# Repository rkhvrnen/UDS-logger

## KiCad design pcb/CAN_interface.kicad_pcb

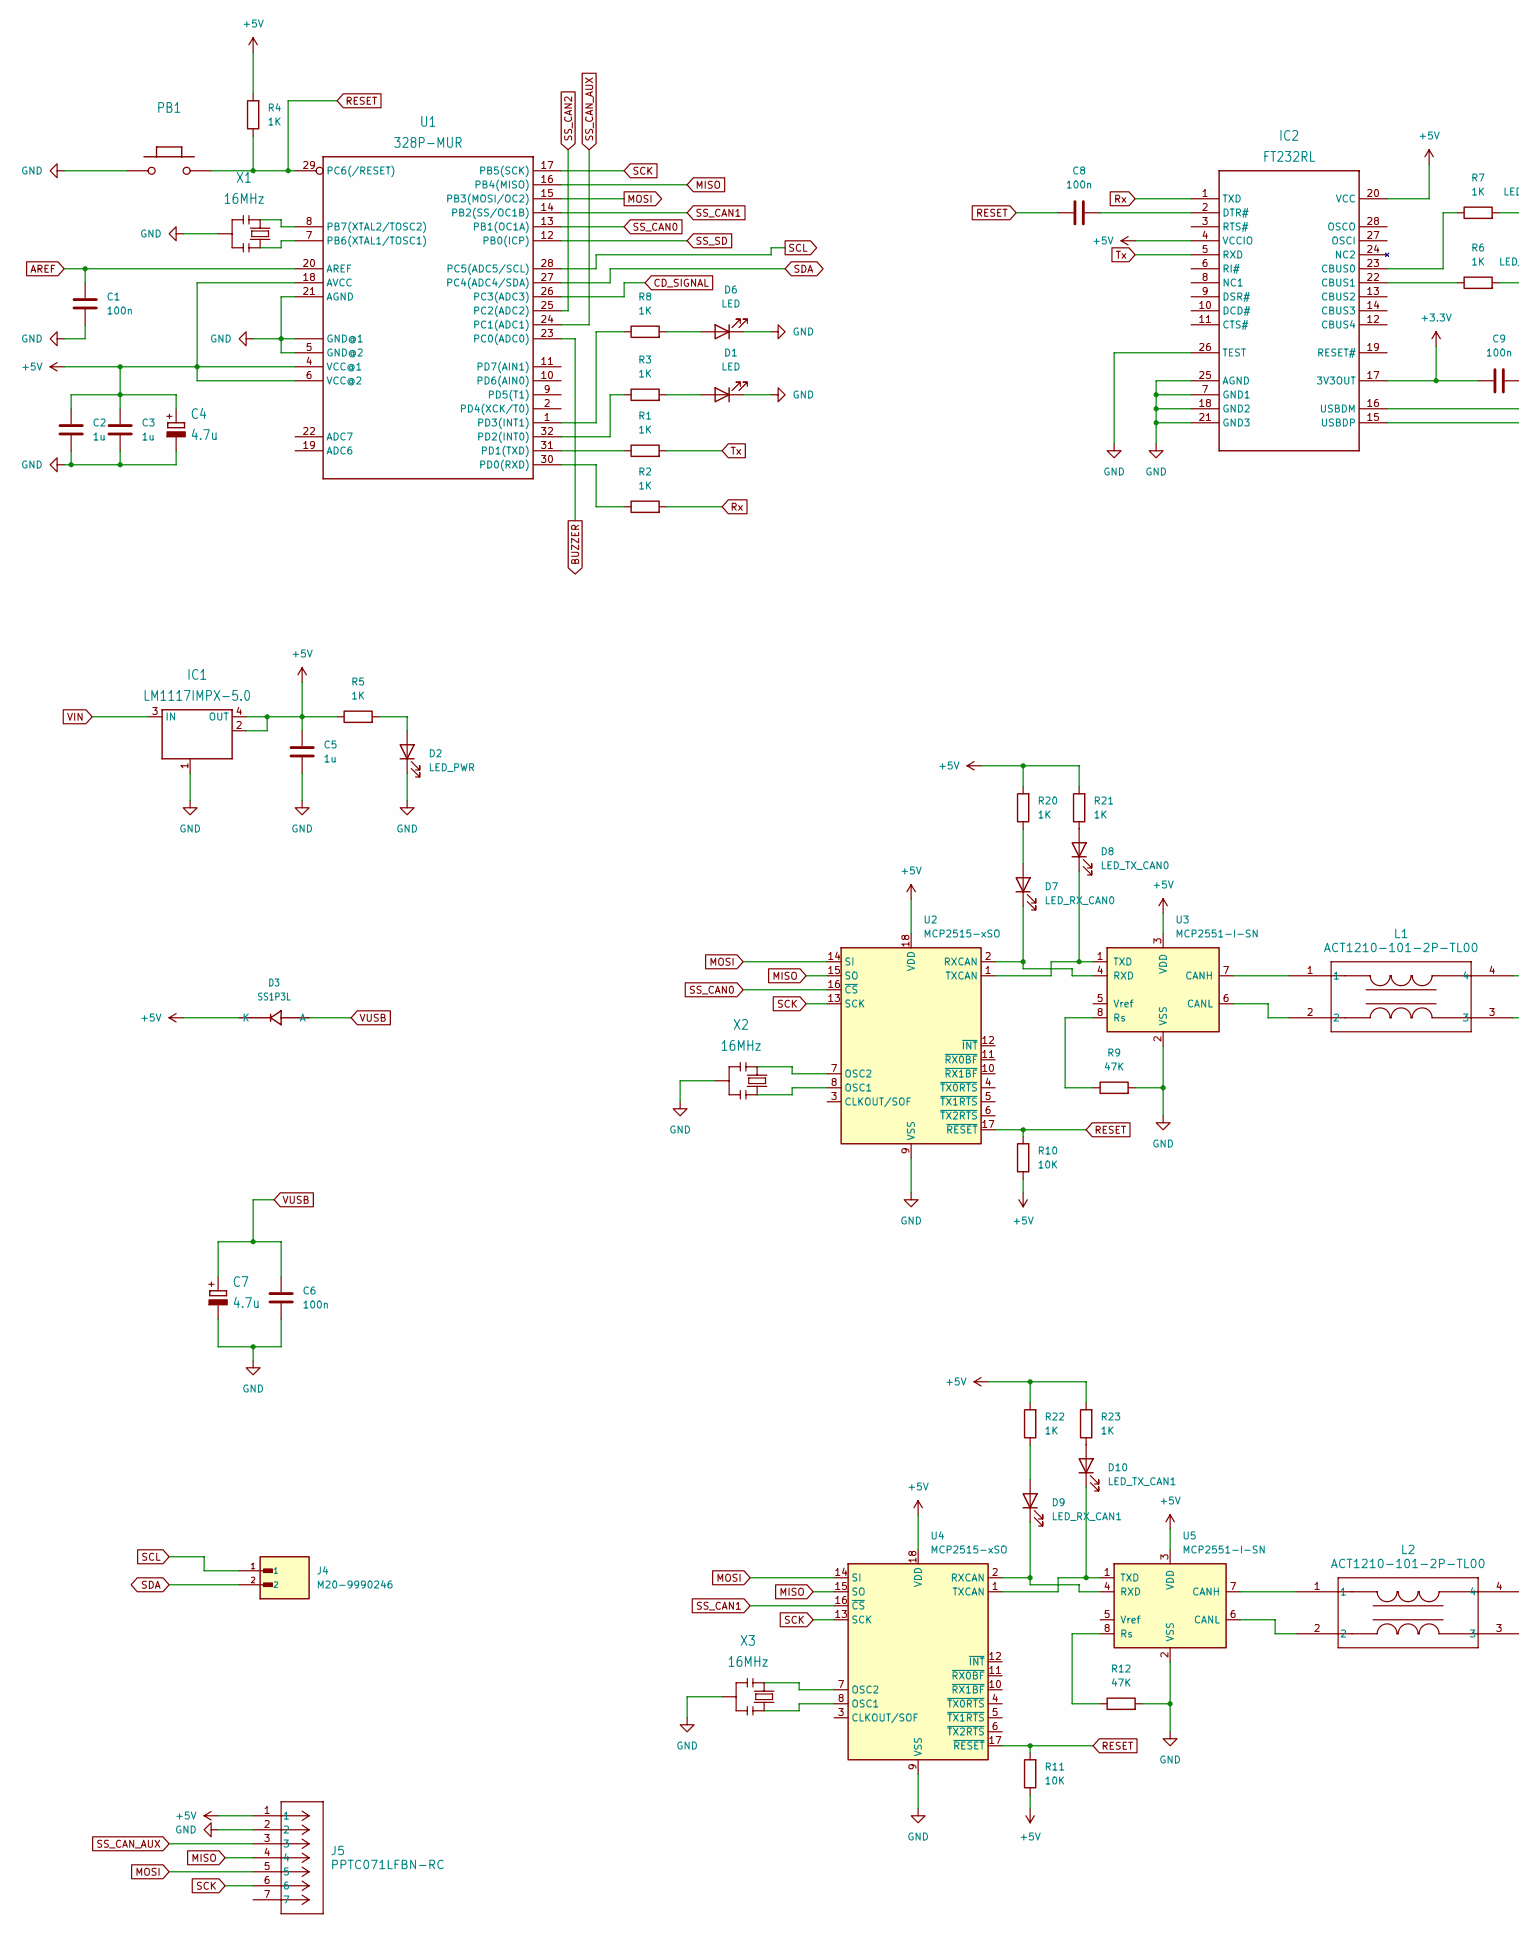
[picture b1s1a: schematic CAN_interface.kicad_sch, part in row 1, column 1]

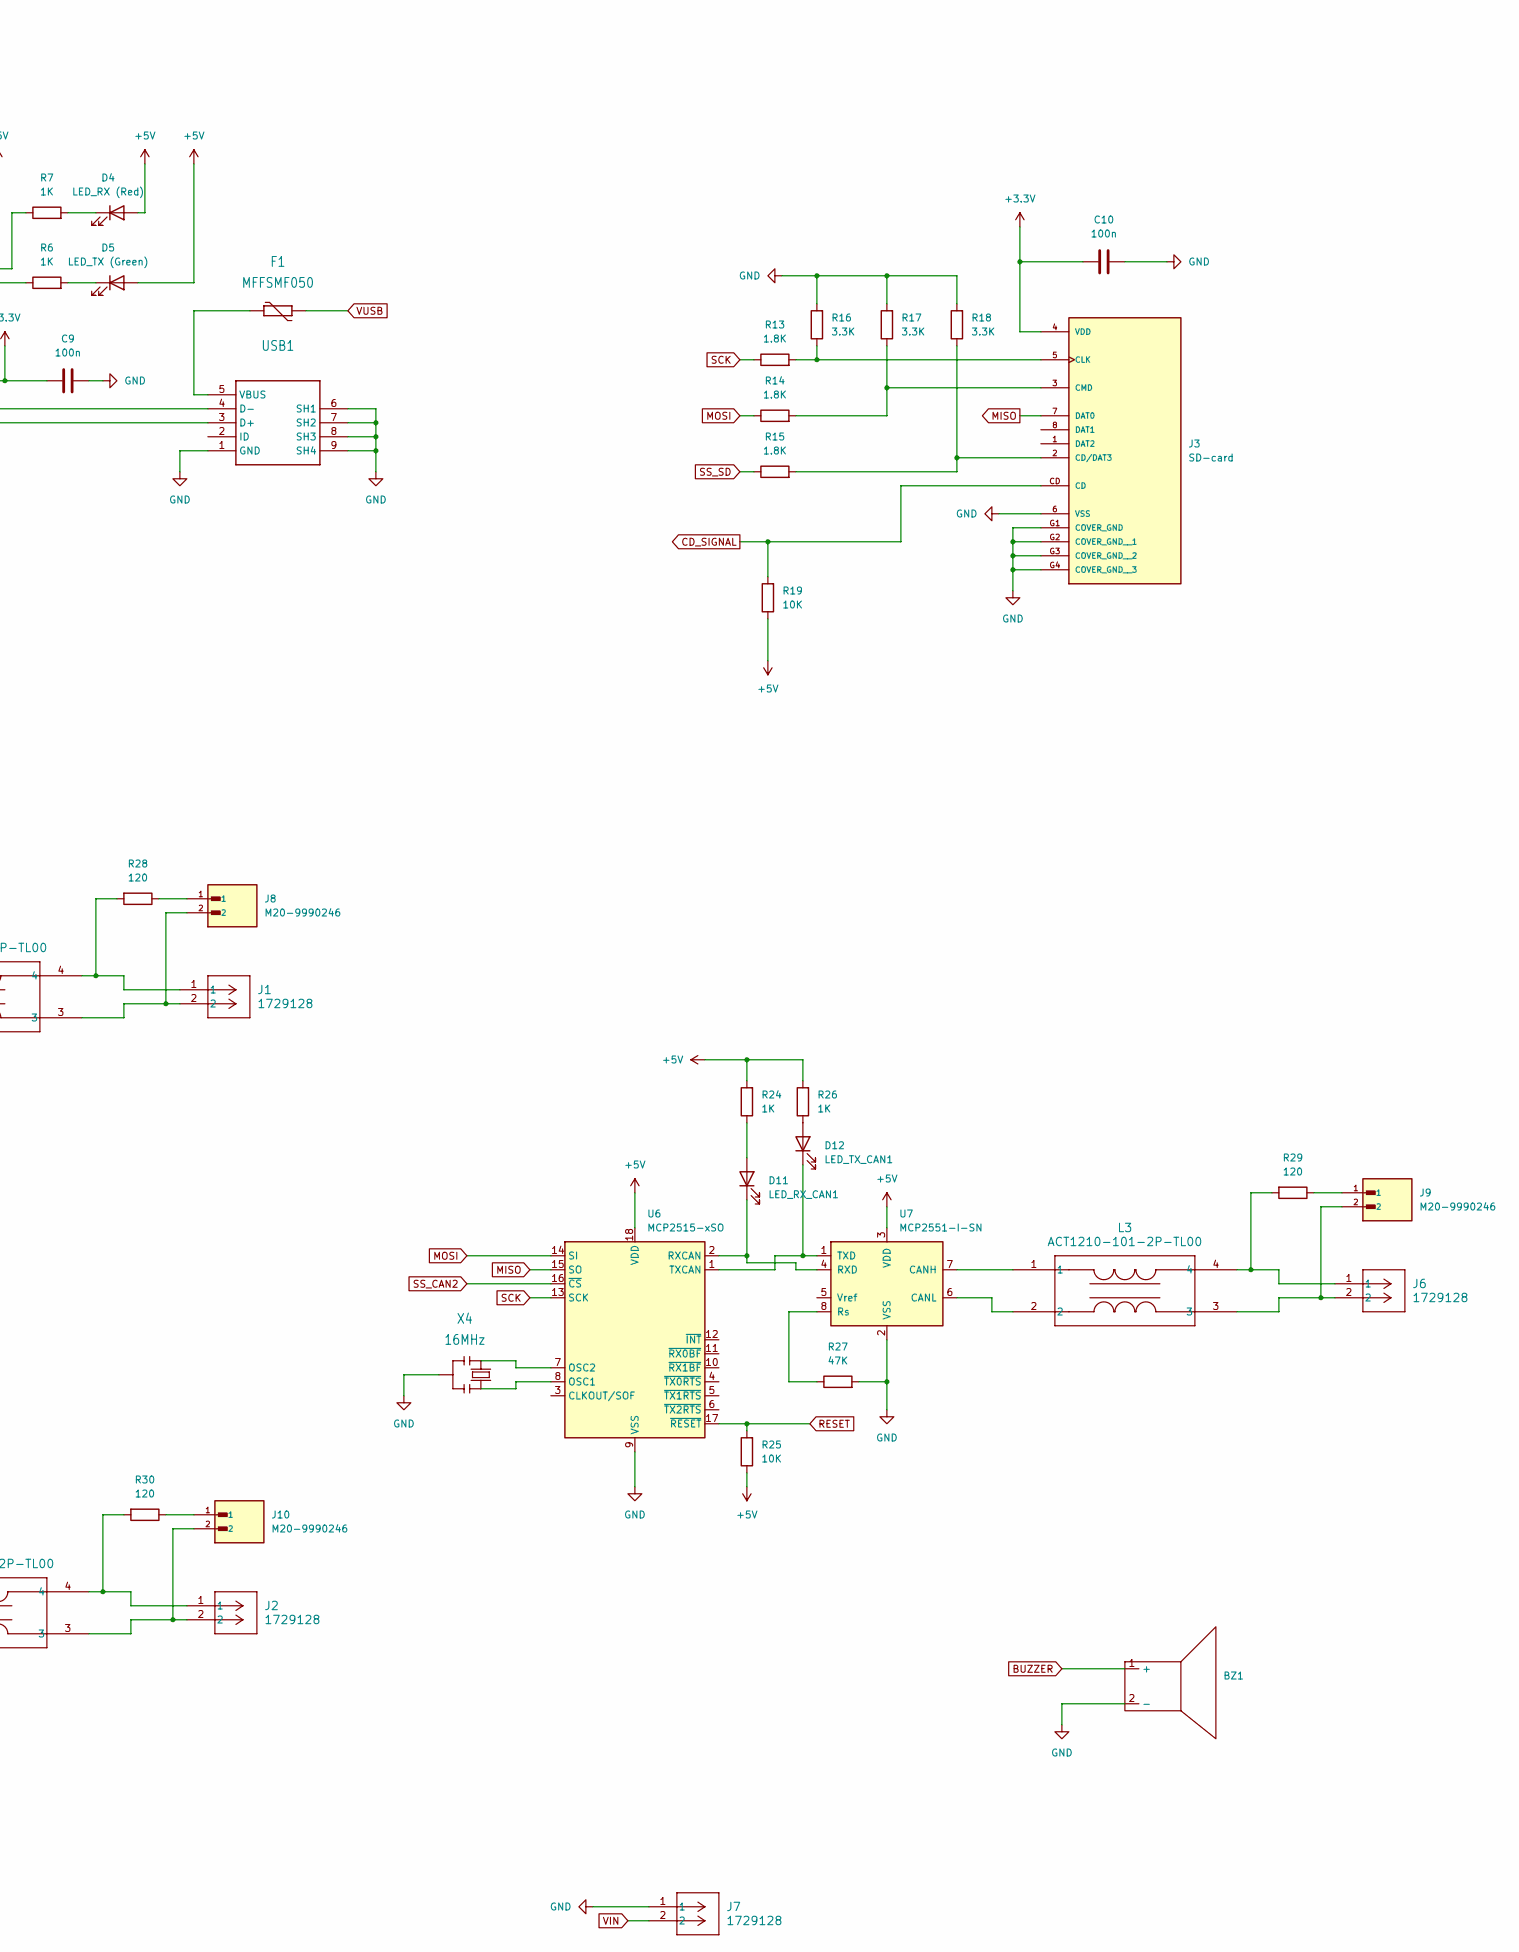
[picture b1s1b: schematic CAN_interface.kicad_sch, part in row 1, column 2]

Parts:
BZ1: Buzzer
C1, C6, C8, C9, C10: 100n; C_0603_1608Metric_Pad1.08x0.95mm_HandSolder
C2, C3, C5: 1u; C_0603_1608Metric_Pad1.08x0.95mm_HandSolder
C4, C7: 4.7u; TAN-A
D1, D6: LED; LED_0603_1608Metric_Pad1.05x0.95mm_HandSolder
D2: LED_PWR; LED_0603_1608Metric_Pad1.05x0.95mm_HandSolder
D3: SS1P3L; DO220AAL
D4: LED_RX (Red); LED_0603_1608Metric_Pad1.05x0.95mm_HandSolder
D5: LED_TX (Green); LED_0603_1608Metric_Pad1.05x0.95mm_HandSolder
D7: LED_RX_CAN0; LED_0603_1608Metric_Pad1.05x0.95mm_HandSolder
D8: LED_TX_CAN0; LED_0603_1608Metric_Pad1.05x0.95mm_HandSolder
D9, D11: LED_RX_CAN1; LED_0603_1608Metric_Pad1.05x0.95mm_HandSolder
D10, D12: LED_TX_CAN1; LED_0603_1608Metric_Pad1.05x0.95mm_HandSolder
F1: MFFSMF050; 0603-1608X90N
IC1: LM1117IMPX-5.0; LINEAR_SOT223
IC2: FT232RL; SSOP28
J1, J2, J6, J7: 1729128; CONN_1729128_PXC
J3: SD-card; CUI_MSD-1-A; PARTREV 1.0
J4, J8, J9, J10: M20-9990246; CONN2_M20-999_1x2_HRW; PARTREV 14
J5: PPTC071LFBN-RC; CONN_xPxC071LFBN-RC_SUL
L1, L2, L3: ACT1210-101-2P-TL00; IND_01-2P-TL00_TDK
PB1: SMD_157SW
R1, R2, R3, R4, R5, R6, R7, R8, R20, R21, R22, R23, R24, R26: 1K; R_0603_1608Metric_Pad0.98x0.95mm_HandSolder
R9, R12, R27: 47K; R_0603_1608Metric_Pad0.98x0.95mm_HandSolder
R10, R11, R19, R25: 10K; R_0603_1608Metric_Pad0.98x0.95mm_HandSolder
R13, R14, R15: 1.8K; R_0603_1608Metric_Pad0.98x0.95mm_HandSolder
R16, R17, R18: 3.3K; R_0603_1608Metric_Pad0.98x0.95mm_HandSolder
R28, R29, R30: 120; R_0603_1608Metric_Pad0.98x0.95mm_HandSolder
U1: 328P-MUR; TQFP32_32A_MCH
U2, U4, U6: MCP2515-xSO; SOIC-18W_7.5x11.6mm_P1.27mm
U3, U5, U7: MCP2551-I-SN; SOIC-8_3.9x4.9mm_P1.27mm
USB1: USB-MINI-B_2
X1, X2, X3, X4: 16MHz; RESONATOR

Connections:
+3.3V: C9.2, C10.1, IC2.17 (3V3OUT), J3.4 (VDD)
+5V: C2.2, C3.2, C4.1 (+), C5.2, D3.P$1 (K), D4.2 (A), D5.2 (A), IC1.2 (OUT@1), IC1.4 (OUT), IC2.4 (VCCIO), IC2.20 (VCC), J5.1, R4.2, R5.1, R10.1, R11.1, R19.1, R20.2, R21.2, R22.2, R23.2, R24.2, R25.1, R26.2, U1.4 (VCC@1), U1.6 (VCC@2), U1.18 (AVCC), U2.18 (VDD), U3.3 (VDD), U4.18 (VDD), U5.3 (VDD), U6.18 (VDD), U7.3 (VDD)
AREF: C1.2, U1.20 (AREF)
BUZZER: BZ1.1 (+), U1.23 (PC0(ADC0))
CD_SIGNAL: J3.CD, R19.2, U1.26 (PC3(ADC3))
GND: BZ1.2 (-), C1.1, C2.1, C3.1, C4.2 (-), C5.1, C6.1, C7.2 (-), C9.1, C10.2, D1.1 (K), D2.1 (K), D6.1 (K), IC1.1 (GND/ADJ), IC2.7 (GND1), IC2.18 (GND2), IC2.21 (GND3), IC2.25 (AGND), IC2.26 (TEST), J3.6 (VSS), J3.G1 (COVER_GND), J3.G2 (COVER_GND__1), J3.G3 (COVER_GND__2), J3.G4 (COVER_GND__3), J5.2, J7.1, PB1.1, R9.2, R12.2, R16.2, R17.2, R18.2, R27.2, U1.3 (GND@1), U1.5 (GND@2), U1.21 (AGND), U1.33 (GND@1), U2.9 (VSS), U3.2 (VSS), U4.9 (VSS), U5.2 (VSS), U6.9 (VSS), U7.2 (VSS), USB1.1 (GND), USB1.6 (SH1), USB1.7 (SH2), USB1.8 (SH3), USB1.9 (SH4), X1.2, X2.2, X3.2, X4.2
MISO: J3.7 (DAT0), J5.4, U1.16 (PB4(MISO)), U2.15 (SO), U4.15 (SO), U6.15 (SO)
MOSI: J5.5, R14.1, U1.15 (PB3(MOSI/OC2)), U2.14 (SI), U4.14 (SI), U6.14 (SI)
unnamed: D1.2 (A), R3.2
unnamed: D2.2 (A), R5.2
unnamed: D4.1 (K), R7.2
unnamed: D5.1 (K), R6.2
unnamed: D6.2 (A), R8.2
unnamed: D7.2 (A), R20.1
unnamed: D7.1 (K), U2.2 (RXCAN), U3.4 (RXD)
unnamed: D8.2 (A), R21.1
unnamed: D8.1 (K), U2.1 (TXCAN), U3.1 (TXD)
unnamed: D9.2 (A), R22.1
unnamed: D9.1 (K), U4.2 (RXCAN), U5.4 (RXD)
unnamed: D10.2 (A), R23.1
unnamed: D10.1 (K), U4.1 (TXCAN), U5.1 (TXD)
unnamed: D11.2 (A), R24.1
unnamed: D11.1 (K), U6.2 (RXCAN), U7.4 (RXD)
unnamed: D12.2 (A), R26.1
unnamed: D12.1 (K), U6.1 (TXCAN), U7.1 (TXD)
unnamed: IC2.23 (CBUS0), R7.1
unnamed: IC2.22 (CBUS1), R6.1
unnamed: C8.1, IC2.2 (DTR#)
unnamed: IC2.16 (USBDM), USB1.4 (D-)
unnamed: IC2.15 (USBDP), USB1.3 (D+)
unnamed: J1.1, L1.4, R28.2
unnamed: J1.2, J8.2, L1.3
unnamed: J2.1, L2.4, R30.2
unnamed: J3.2 (CD/DAT3), R15.2, R18.1
unnamed: J3.5 (CLK), R13.2, R16.1
unnamed: J3.3 (CMD), R14.2, R17.1
unnamed: J6.1, L3.4, R29.2
unnamed: J6.2, J9.2, L3.3
unnamed: J8.1, R28.1
unnamed: J9.1, R29.1
unnamed: J10.1, R30.1
unnamed: J2.2, J10.2, L2.3
unnamed: U1.7 (PB6(XTAL1/TOSC1)), X1.3
unnamed: U1.8 (PB7(XTAL2/TOSC2)), X1.1
unnamed: R2.1, U1.30 (PD0(RXD))
unnamed: R1.1, U1.31 (PD1(TXD))
unnamed: R3.1, U1.32 (PD2(INT0))
unnamed: R8.1, U1.1 (PD3(INT1))
unnamed: U2.8 (OSC1), X2.3
unnamed: U2.7 (OSC2), X2.1
unnamed: L1.1, U3.7 (CANH)
unnamed: L1.2, U3.6 (CANL)
unnamed: R9.1, U3.8 (Rs)
unnamed: U4.8 (OSC1), X3.3
unnamed: U4.7 (OSC2), X3.1
unnamed: L2.1, U5.7 (CANH)
unnamed: L2.2, U5.6 (CANL)
unnamed: R12.1, U5.8 (Rs)
unnamed: U6.8 (OSC1), X4.3
unnamed: U6.7 (OSC2), X4.1
unnamed: L3.1, U7.7 (CANH)
unnamed: L3.2, U7.6 (CANL)
unnamed: R27.1, U7.8 (Rs)
unnamed: F1.2, USB1.5 (VBUS)
RESET: C8.2, PB1.2, R4.1, R10.2, R11.2, R25.2, U1.29 (PC6(/RESET)), U2.17 (~RESET), U4.17 (~RESET), U6.17 (~RESET)
Rx: IC2.1 (TXD), R2.2
SCK: J5.6, R13.1, U1.17 (PB5(SCK)), U2.13 (SCK), U4.13 (SCK), U6.13 (SCK)
SCL: J4.1, U1.28 (PC5(ADC5/SCL))
SDA: J4.2, U1.27 (PC4(ADC4/SDA))
SS_CAN0: U1.13 (PB1(OC1A)), U2.16 (~CS)
SS_CAN1: U1.14 (PB2(SS/OC1B)), U4.16 (~CS)
SS_CAN2: U1.25 (PC2(ADC2)), U6.16 (~CS)
SS_CAN_AUX: J5.3, U1.24 (PC1(ADC1))
SS_SD: R15.1, U1.12 (PB0(ICP))
Tx: IC2.5 (RXD), R1.2
VIN: IC1.3 (IN), J7.2
VUSB: C6.2, C7.1 (+), D3.P$2 (A), F1.1

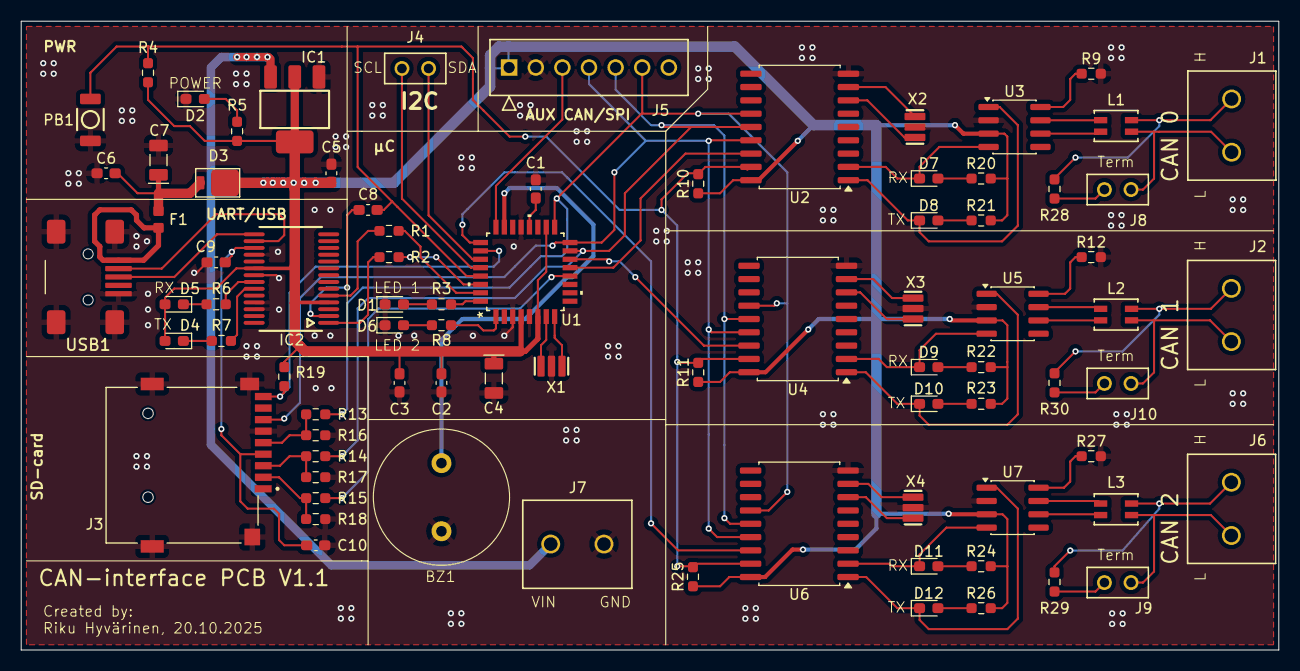
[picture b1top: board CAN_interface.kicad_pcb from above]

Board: 2 copper layers, 120.0 x 60.0 mm, 82 parts (0 on the bottom side), 77 nets.

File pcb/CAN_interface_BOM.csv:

"Id";"Designator";"Footprint";"Quantity";"Designation";"Supplier and ref";
1;"X3,X1,X4,X2";"RESONATOR";4;"16MHz";;;
2;"R21,R8,R5,R4,R7,R26,R2,R20,R24,R6,R22,R1,R23,R3";"R_0603_1608Metric_Pad0.98x0.95mm_HandSolder";14;"1K";;;
3;"R27,R9,R12";"R_0603_1608Metric_Pad0.98x0.95mm_HandSolder";3;"47K";;;
4;"J8,J4,J10,J9";"CONN2_M20-999_1x2_HRW";4;"M20-9990246";;;
5;"C4,C7";"TAN-A";2;"4.7u";;;
6;"BZ1";"Buzzer";1;"~";;;
7;"R13,R14,R15";"R_0603_1608Metric_Pad0.98x0.95mm_HandSolder";3;"1.8K";;;
8;"PB1";"SMD_157SW";1;"~";;;
9;"U5,U7,U3";"SOIC-8_3.9x4.9mm_P1.27mm";3;"MCP2551-I-SN";;;
10;"C10,C6,C1,C8,C9";"C_0603_1608Metric_Pad1.08x0.95mm_HandSolder";5;"100n";;;
11;"C3,C2,C5";"C_0603_1608Metric_Pad1.08x0.95mm_HandSolder";3;"1u";;;
12;"R16,R17,R18";"R_0603_1608Metric_Pad0.98x0.95mm_HandSolder";3;"3.3K";;;
13;"IC1";"LINEAR_SOT223";1;"LM1117IMPX-5.0";;;
14;"D4";"LED_0603_1608Metric_Pad1.05x0.95mm_HandSolder";1;"LED_RX (Red)";;;
15;"U2,U4,U6";"SOIC-18W_7.5x11.6mm_P1.27mm";3;"MCP2515-xSO";;;
16;"D3";"DO220AAL";1;"SS1P3L";;;
17;"D1,D6";"LED_0603_1608Metric_Pad1.05x0.95mm_HandSolder";2;"LED";;;
18;"D12,D10";"LED_0603_1608Metric_Pad1.05x0.95mm_HandSolder";2;"LED_TX_CAN1";;;
19;"L3,L1,L2";"IND_01-2P-TL00_TDK";3;"ACT1210-101-2P-TL00";;;
20;"R10,R11,R25,R19";"R_0603_1608Metric_Pad0.98x0.95mm_HandSolder";4;"10K";;;
21;"D7";"LED_0603_1608Metric_Pad1.05x0.95mm_HandSolder";1;"LED_RX_CAN0";;;
22;"J6,J7,J2,J1";"CONN_1729128_PXC";4;"1729128";;;
23;"R28,R30,R29";"R_0603_1608Metric_Pad0.98x0.95mm_HandSolder";3;"120";;;
24;"D2";"LED_0603_1608Metric_Pad1.05x0.95mm_HandSolder";1;"LED_PWR";;;
25;"J5";"CONN_xPxC071LFBN-RC_SUL";1;"PPTC071LFBN-RC";;;
26;"F1";"0603-1608X90N";1;"MFFSMF050";;;
27;"D5";"LED_0603_1608Metric_Pad1.05x0.95mm_HandSolder";1;"LED_TX (Green)";;;
28;"D9,D11";"LED_0603_1608Metric_Pad1.05x0.95mm_HandSolder";2;"LED_RX_CAN1";;;
29;"J3";"CUI_MSD-1-A";1;"SD-card";;;
30;"USB1";"USB-MINI-B_2";1;"~";;;
31;"U1";"TQFP32_32A_MCH";1;"328P-MUR";;;
32;"IC2";"SSOP28";1;"FT232RL";;;
33;"D8";"LED_0603_1608Metric_Pad1.05x0.95mm_HandSolder";1;"LED_TX_CAN0";;;

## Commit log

2025-09-10 Table-tested version with CR6EU5 control unit
    UART dataflow as ASCII representation.
2025-09-10 Python reading script added
2025-09-20 GUI + bug fix
    -Implementation of plotting GUI started
    -Fixed bug regarding the loss of the least significant byte of the UDS response message
    -CAN communication functions modified to be more modular and support multiple separate CAN controllers
2025-09-21 Code improvements
    UDS handling moved to separate source file for more modular code structure
2025-09-21 Minor optimizations
2025-09-21 SD card saving implemented
2025-10-02 Lots of improvements and new features
    - Telematics interface implemented for logfile timestamp generation and enable data acquisition control from COMAND controller button
    - GUI plotter advanced, not ready yet
2025-10-06 GUI development
2025-10-07 UI improvements
    Plotting finally works
2025-10-14 PCB design files added
    Schema drawn
2025-10-16 Update .gitignore
    Ignore KiCad cache files
2025-10-16 PCB V1.0
    Added PCB V1.0 design and gerber files
2025-10-16 Create PCB_V1.0.png
    Added picture of V1.0 PCB
2025-10-21 PCB improvements
    0201 SMD components replaced with 0603.
    Reset line drawn for MCP2515.
    Silkscreen improvements.
    Other small improvements.
